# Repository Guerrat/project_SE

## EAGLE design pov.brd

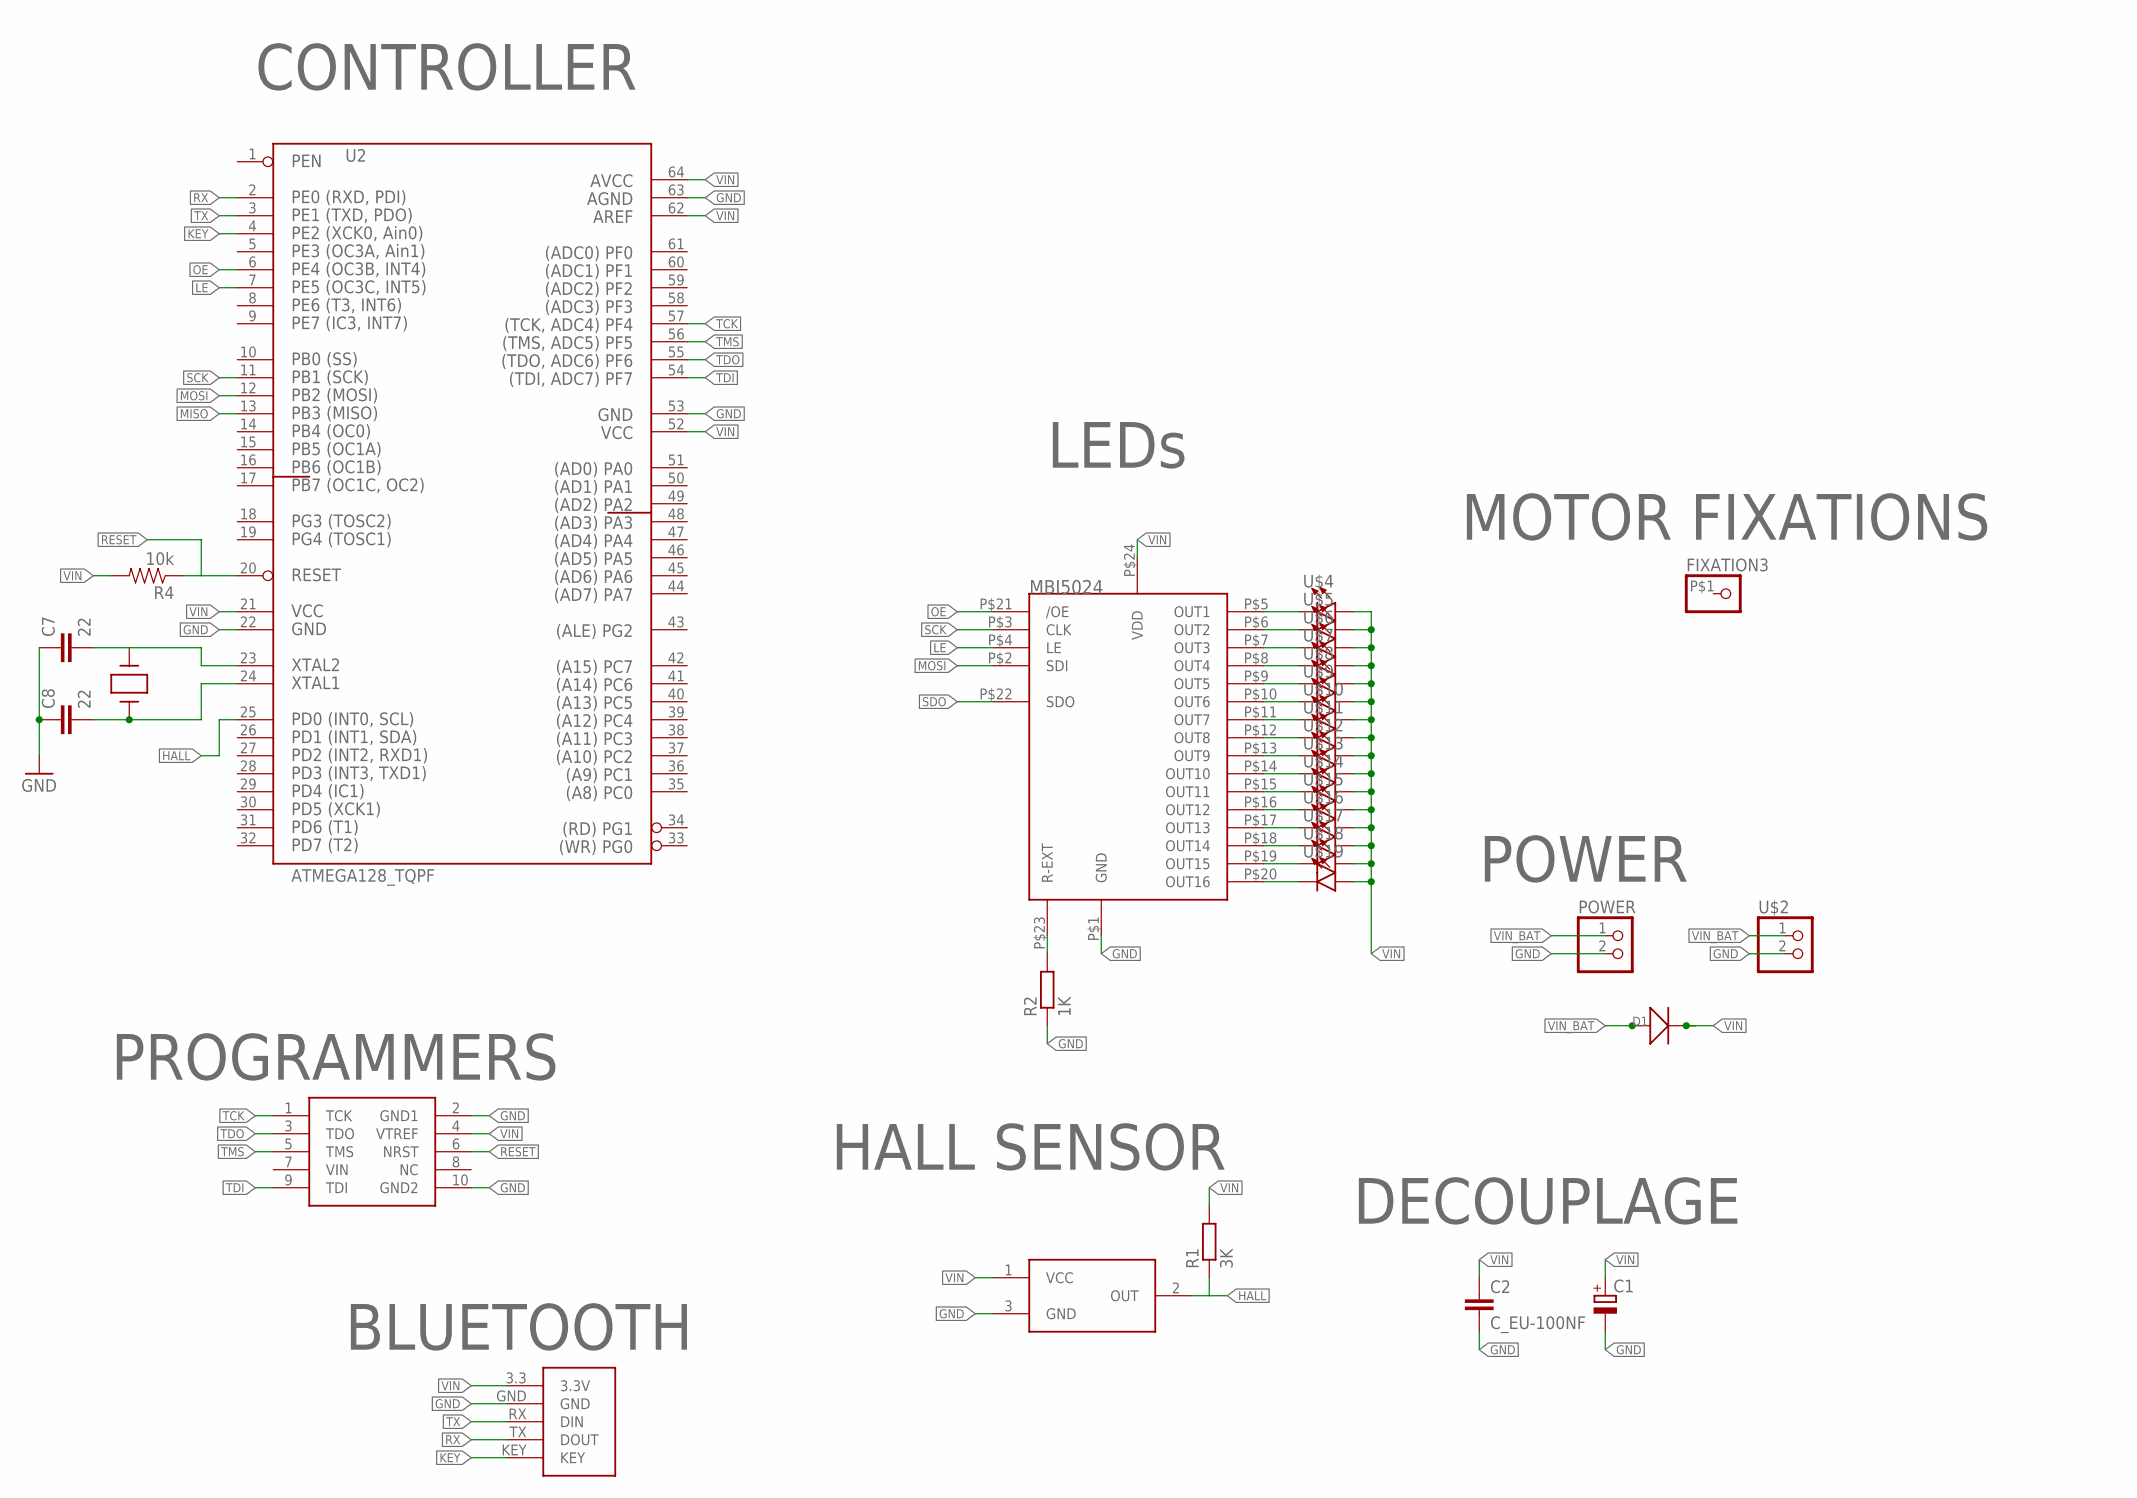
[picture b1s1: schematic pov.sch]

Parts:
C1: CPOL_EU-680UF_25V; E3,5-8
C2: C_EU-100NF; C0805
C7, C8: 22; C0603
D1: D-SOD-123; SOD123
FIXATION3: CONNEC_1X01SHAFT; SHAFT2
JTAG: AVR_JTAG
POWER: CONNEC_1X02BASIC; CONNEC_1X02
R1: 3K; R0805
R2: 1K; R0805
R4: 10k; 0805
U1: MBI5024; SOP24L-300-1.0
U2: ATMEGA128_TQPF; TQFP64
U$1: DRV5023FAEDBZRQ1; SOT-23
U$2: CONNEC_1X02; JST_GH_2P
U$4, U$5, U$6, U$7, U$8, U$9, U$10, U$11, U$12, U$13, U$14, U$15, U$16, U$17, U$18, U$19: LED1206; LED-1206
U$23: HC05; HC-05
XTAL1: QUARTZ; HC49US

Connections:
GND: C1.-, C2.2, C7.1, C8.1, JTAG.2 (GND1), JTAG.10 (GND2), POWER.2, R2.1, U1.P$1 (GND), U2.22, U2.53, U2.63, U$1.3 (GND), U$2.2, U$23.GND
HALL: R1.1, U2.25, U$1.2 (OUT)
KEY: U2.4, U$23.KEY
LE: U1.P$4 (LE), U2.7
MISO: U2.13
MOSI: U1.P$2 (SDI), U2.12
unnamed: U1.P$5 (OUT1), U$4.C
unnamed: U1.P$6 (OUT2), U$5.C
unnamed: U1.P$7 (OUT3), U$6.C
unnamed: U1.P$8 (OUT4), U$7.C
unnamed: U1.P$9 (OUT5), U$8.C
unnamed: U1.P$10 (OUT6), U$9.C
unnamed: U1.P$11 (OUT7), U$10.C
unnamed: U1.P$12 (OUT8), U$11.C
unnamed: U1.P$13 (OUT9), U$12.C
unnamed: U1.P$14 (OUT10), U$13.C
unnamed: U1.P$15 (OUT11), U$14.C
unnamed: U1.P$16 (OUT12), U$15.C
unnamed: U1.P$17 (OUT13), U$16.C
unnamed: U1.P$18 (OUT14), U$17.C
unnamed: U1.P$19 (OUT15), U$18.C
unnamed: U1.P$20 (OUT16), U$19.C
unnamed: R2.2, U1.P$23 (R-EXT)
unnamed: C7.2, U2.23, XTAL1.2
unnamed: C8.2, U2.24, XTAL1.1
OE: U1.P$21 (/OE), U2.6
RESET: JTAG.6 (NRST), R4.1, U2.20
RX: U2.2, U$23.TX (DOUT)
SCK: U1.P$3 (CLK), U2.11
SDO: U1.P$22 (SDO)
TCK: JTAG.1 (TCK), U2.57
TDI: JTAG.9 (TDI), U2.54
TDO: JTAG.3 (TDO), U2.55
TMS: JTAG.5 (TMS), U2.56
TX: U2.3, U$23.RX (DIN)
VIN: C1.+, C2.1, D1.-, JTAG.4 (VTREF), R1.2, R4.2, U1.P$24 (VDD), U2.21, U2.52, U2.62, U2.64, U$1.1 (VCC), U$4.A, U$5.A, U$6.A, U$7.A, U$8.A, U$9.A, U$10.A, U$11.A, U$12.A, U$13.A, U$14.A, U$15.A, U$16.A, U$17.A, U$18.A, U$19.A, U$23.3.3 (3.3V)
VIN_BAT: D1.+, POWER.1, U$2.1

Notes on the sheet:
CONTROLLER
LEDs
HALL SENSOR
PROGRAMMERS
BLUETOOTH
MOTOR FIXATIONS
DECOUPLAGE
POWER
MBI5024

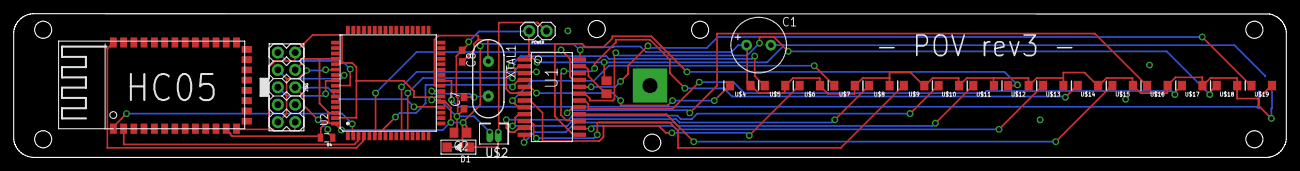
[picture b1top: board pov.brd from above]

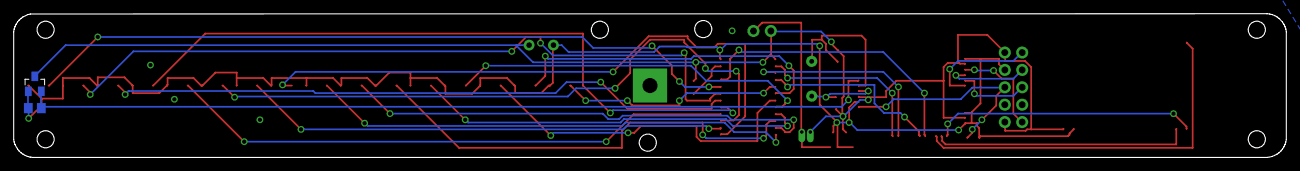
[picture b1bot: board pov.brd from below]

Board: 2 copper layers, 186.0 x 21.0 mm, 33 parts (2 on the bottom side), 35 nets.

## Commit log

2019-11-13 Code
2019-11-13 echo ok
2019-11-14 uart pas ok
2019-11-19 com usart ok
2019-11-27 bt ok
2019-11-27 spi ok
2019-11-27 hall ok
2019-12-04 timer
2019-12-10 begin of timer
2019-12-17 patterns
2019-12-17 Avec timer 0

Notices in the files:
parts and their libraries:
SparkFun-Passives: Licensing: CC v3.0 Share-Alike You are welcome to use this library for commercial purposes.
SparkFun-LED: Licensing: Creative Commons ShareAlike 4.0 International - https://creativecommons.org/licenses/by-sa/4.0
